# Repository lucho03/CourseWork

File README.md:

# CourseWork

A device that counts your repeats when you do some exercise.

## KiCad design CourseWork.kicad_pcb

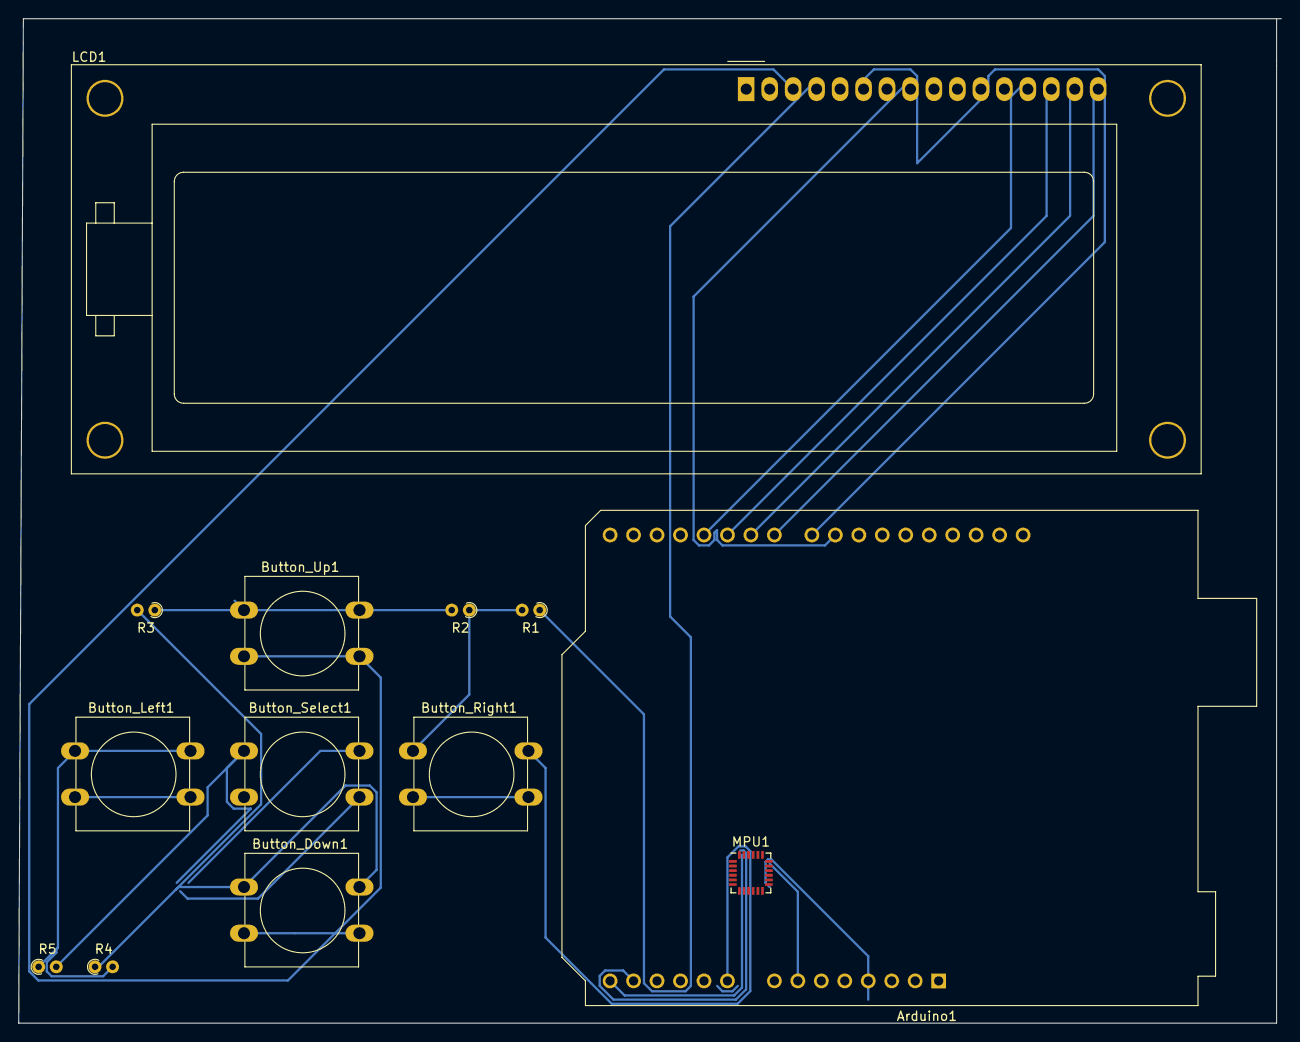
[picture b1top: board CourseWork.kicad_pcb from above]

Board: 2 copper layers, 136.7 x 108.7 mm, 13 parts (0 on the bottom side), 17 nets.

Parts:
Arduino1: Arduino_UNO_R3
Button_Down1: SW_Push; SW_PUSH-12mm
Button_Left1: SW_Push; SW_PUSH-12mm
Button_Right1: SW_Push; SW_PUSH-12mm
Button_Select1: SW_Push; SW_PUSH-12mm
Button_Up1: SW_Push; SW_PUSH-12mm
LCD1: HY1602E
MPU1: MPU-6050; InvenSense_QFN-24_4x4mm_P0.5mm
R1: 2K; R_Axial_DIN0204_L3.6mm_D1.6mm_P1.90mm_Vertical
R2: 330R; R_Axial_DIN0204_L3.6mm_D1.6mm_P1.90mm_Vertical
R3: 620R; R_Axial_DIN0204_L3.6mm_D1.6mm_P1.90mm_Vertical
R4: 1K; R_Axial_DIN0204_L3.6mm_D1.6mm_P1.90mm_Vertical
R5: 3K3; R_Axial_DIN0204_L3.6mm_D1.6mm_P1.90mm_Vertical

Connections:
+5V: LCD1.4, R1.1
GND: Button_Down1.2, Button_Left1.2, Button_Right1.2, Button_Select1.2, Button_Up1.2, LCD1.3, LCD1.7
unnamed: Arduino1.4, MPU1.13
unnamed: Arduino1.7, MPU1.18
unnamed: Arduino1.9, Button_Right1.1, R1.2, R2.1
unnamed: Arduino1.13, MPU1.24
unnamed: Arduino1.14, MPU1.23
unnamed: Arduino1.19, LCD1.13
unnamed: Arduino1.20, LCD1.14
unnamed: Arduino1.21, LCD1.15
unnamed: Arduino1.22, LCD1.16
unnamed: Arduino1.23, LCD1.6
unnamed: Arduino1.24, LCD1.8
unnamed: Button_Down1.1, R3.2, R4.1
unnamed: Button_Left1.1, R4.2, R5.1
unnamed: Button_Select1.1, R5.2
unnamed: Button_Up1.1, R2.2, R3.1

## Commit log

2021-05-19 Kicad
    Pcb and schema
2021-05-19 Update README.md
    Rewrite README
2021-05-19 Update CourseWork.ino
    Finall code!
